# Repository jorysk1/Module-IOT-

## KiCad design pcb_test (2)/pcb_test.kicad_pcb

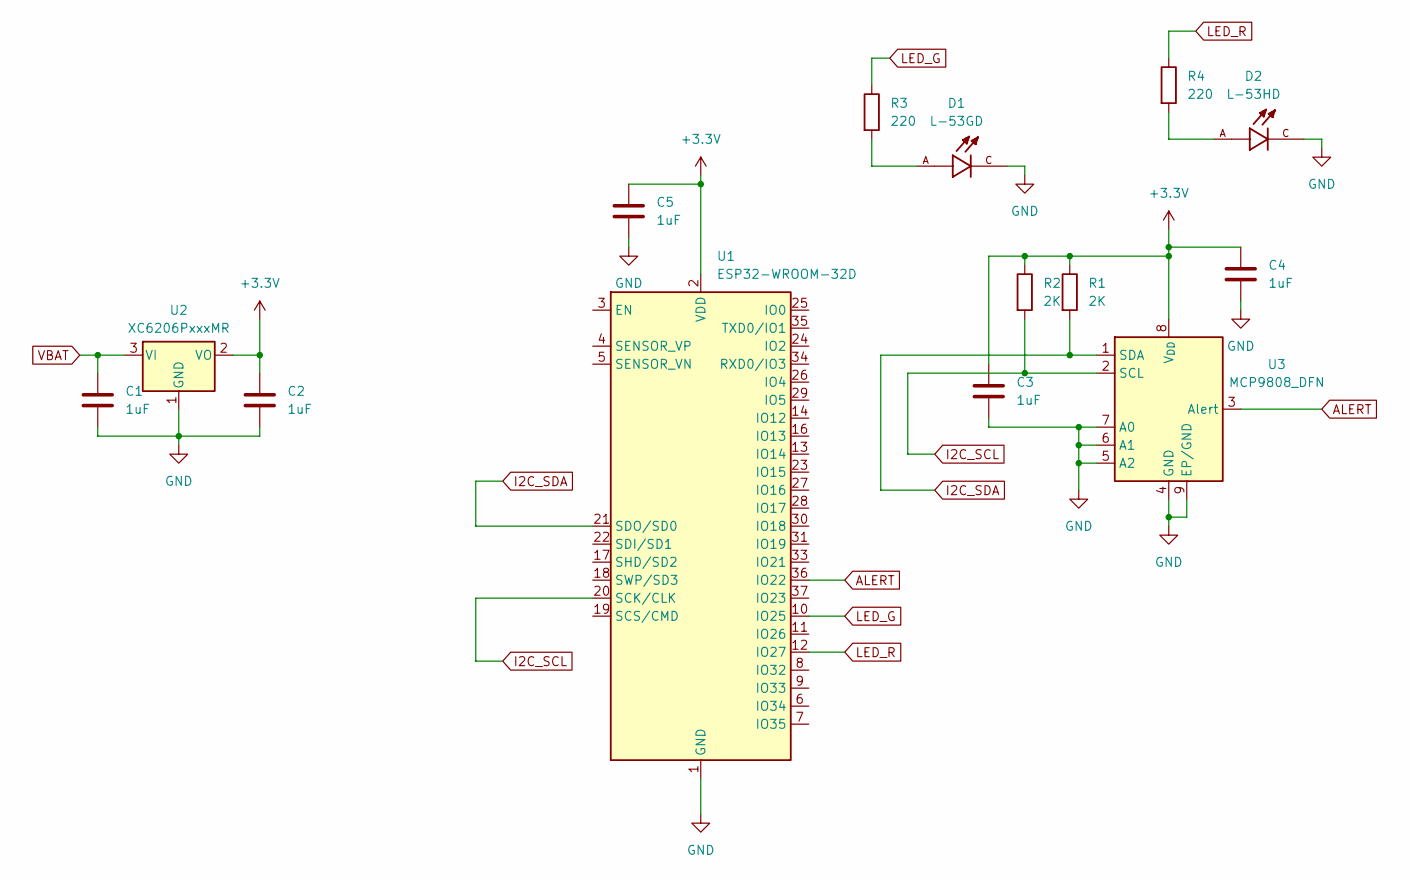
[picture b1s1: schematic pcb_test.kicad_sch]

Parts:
C1, C2, C3, C4, C5: 1uF; C_0201_0603Metric
D1: L-53GD; LEDRD254W50D500H1060; PARTREV V.3
D2: L-53HD; LED_WP7113SYD; PARTREV V.3
R1, R2: 2K; R_0201_0603Metric
R3, R4: 220; R_0201_0603Metric
U1: ESP32-WROOM-32D
U2: XC6206PxxxMR; SOT-23-3
U3: MCP9808_DFN; DFN-8-1EP_3x2mm_P0.5mm_EP1.7x1.4mm

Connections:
+3.3V: C2.1, C3.1, C4.1, C5.1, R1.1, R2.1, U1.2 (VDD), U2.2 (VO), U3.8 (V_{DD})
ALERT: U1.36 (IO22), U3.3 (Alert)
GND: C1.2, C2.2, C3.2, C4.2, C5.2, D1.C, D2.C, U1.1 (GND), U1.15 (GND), U1.38 (GND), U1.39 (GND), U2.1 (GND), U3.4 (GND), U3.5 (A2), U3.6 (A1), U3.7 (A0), U3.9 (EP/GND)
I2C_SCL: R2.2, U1.20 (SCK/CLK), U3.2 (SCL)
I2C_SDA: R1.2, U1.21 (SDO/SD0), U3.1 (SDA)
LED_G: R3.1, U1.10 (IO25)
LED_R: R4.1, U1.12 (IO27)
unnamed: D1.A, R3.2
unnamed: D2.A, R4.2
VBAT: C1.1, U2.3 (VI)

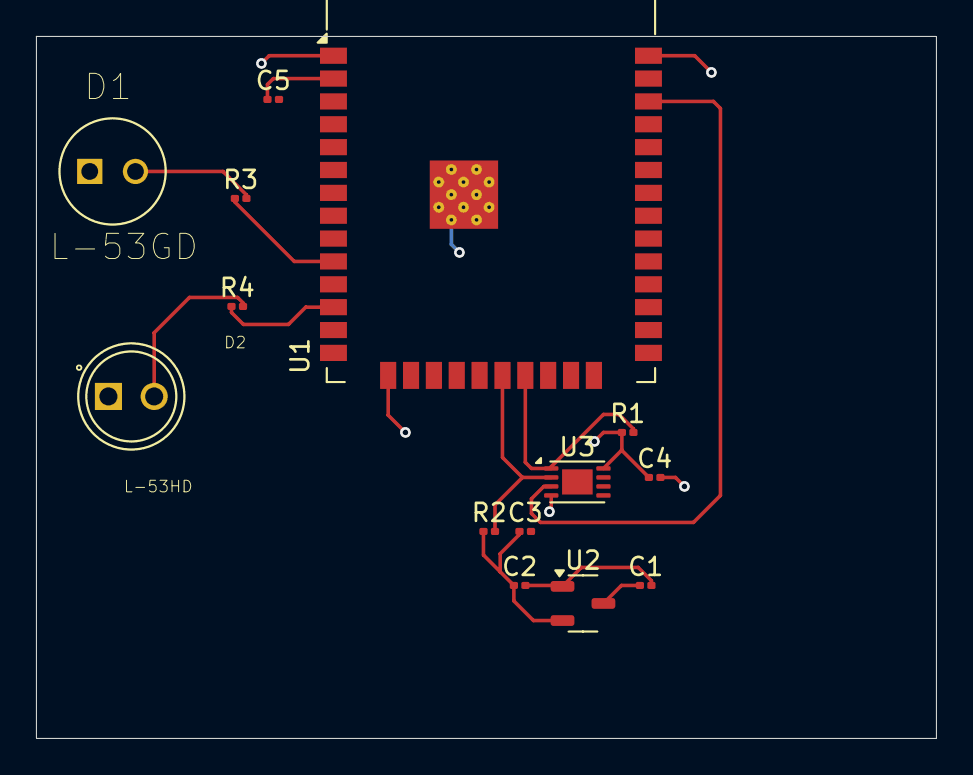
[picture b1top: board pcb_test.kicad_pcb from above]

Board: 2 copper layers, 50.0 x 39.0 mm, 14 parts (0 on the bottom side), 10 nets.
